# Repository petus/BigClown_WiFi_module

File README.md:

# BigClown WiFi module v1.0</br>
WiFi module for BigClown platform</br>
</br>
This WiFi module is developed for BigClown IoT platform. The WiFi module can be ESP07 or ESP12E (ESP8266 IC).</br>
</br>
How to use WiFi module for BigClown </br>
(czech language) - https://chiptron.cz/articles.php?article_id=182</br>
(english) - https://time4ee.com/articles.php?article_id=113</br>
</br>
The Wi-Fi module is supported by BigClown SDK</br>
https://github.com/bigclownlabs/bcf-sdk/blob/master/bcl/src/bc_esp8266.c</br>
Example with Wi-Fi module</br>
https://github.com/bigclownprojects/bcf-wifi-cryptoclock</br>

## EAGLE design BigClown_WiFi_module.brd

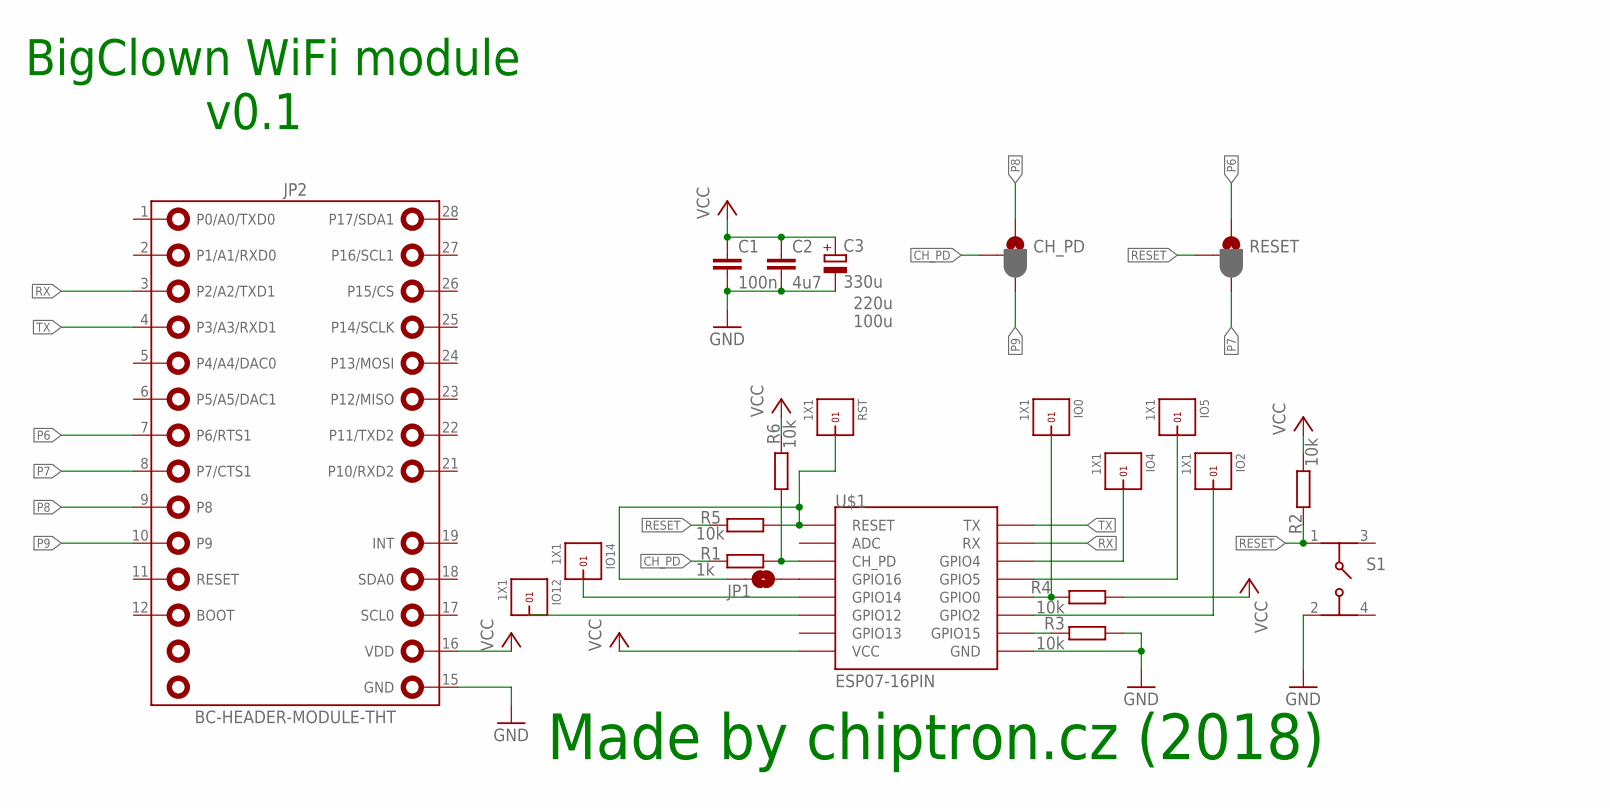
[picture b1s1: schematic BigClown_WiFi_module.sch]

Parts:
C1: 100n; C0805
C2: 4u7; C1812K
C3: 330u; D/7343-31R
CH_PD: JUMPER-SMT_3_1-NC_PASTE_SILK; SMT-JUMPER_3_1-NC_PASTE_SILK
IO0, IO2, IO4, IO5, IO12, IO14: 1X1
JP1: JUMPER-SMT_2_NO_NO-SILK; SMT-JUMPER_2_NO_NO-SILK
JP2: BC-HEADER-MODULE-THT
R1: 1k; M0805
R2, R3, R4, R5, R6: 10k; M0805
RESET: JUMPER-SMT_3_1-NC_PASTE_SILK; SMT-JUMPER_3_1-NC_PASTE_SILK
RST: 1X1
S1: 430152043826
U$1: ESP07-16PIN

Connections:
CH_PD: CH_PD.2, R1.1
GND: C1.2, C2.2, C3.-, JP2.15 (GND), R3.1, S1.2, U$1.GND
unnamed: R1.2, R6.1, U$1.CH_PD
unnamed: IO0.1, R4.2, U$1.GPIO0
unnamed: R3.2, U$1.GPIO15
unnamed: JP1.1, R5.2, RST.1, U$1.REST (RESET)
unnamed: JP1.2, U$1.GPIO16
unnamed: IO12.1, U$1.GPIO12
unnamed: IO14.1, U$1.GPIO14
unnamed: IO4.1, U$1.GPIO4
unnamed: IO5.1, U$1.GPIO5
unnamed: IO2.1, U$1.GPIO2
P6: JP2.7 (P6/RTS1), RESET.1
P7: JP2.8 (P7/CTS1), RESET.3
P8: CH_PD.1, JP2.9 (P8)
P9: CH_PD.3, JP2.10 (P9)
RESET: R2.1, R5.1, RESET.2, S1.1
RX: JP2.3 (P2/A2/TXD1), U$1.RX
TX: JP2.4 (P3/A3/RXD1), U$1.TX
VCC: C1.1, C2.1, C3.+, JP2.16 (VDD), R2.2, R4.1, R6.2, U$1.VCC

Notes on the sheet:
BigClown WiFi module
v0.1
Made by chiptron.cz (2018)
100u
220u

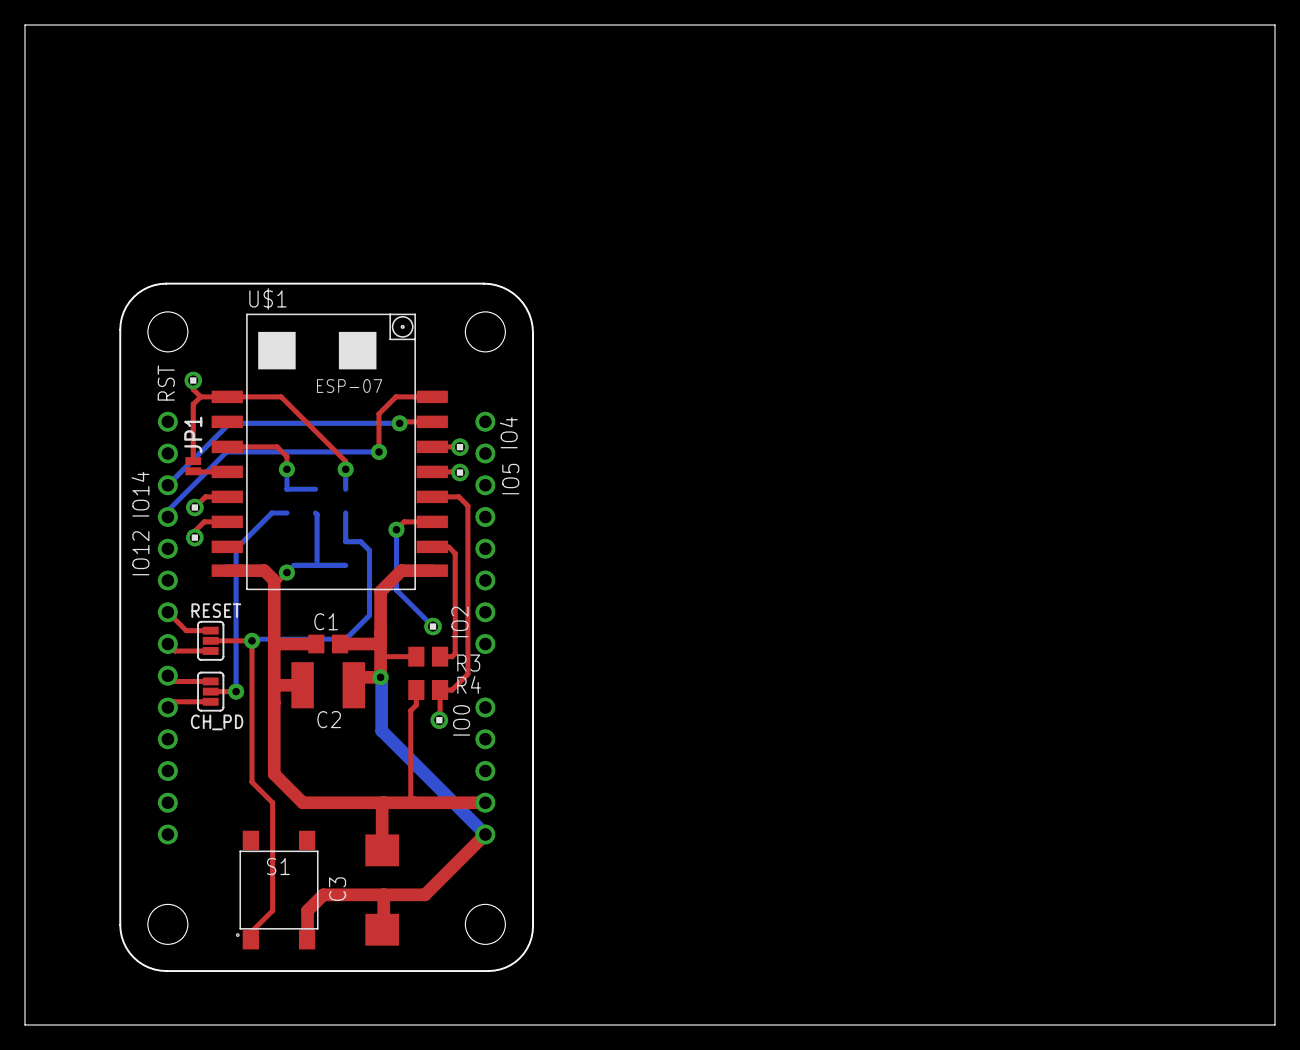
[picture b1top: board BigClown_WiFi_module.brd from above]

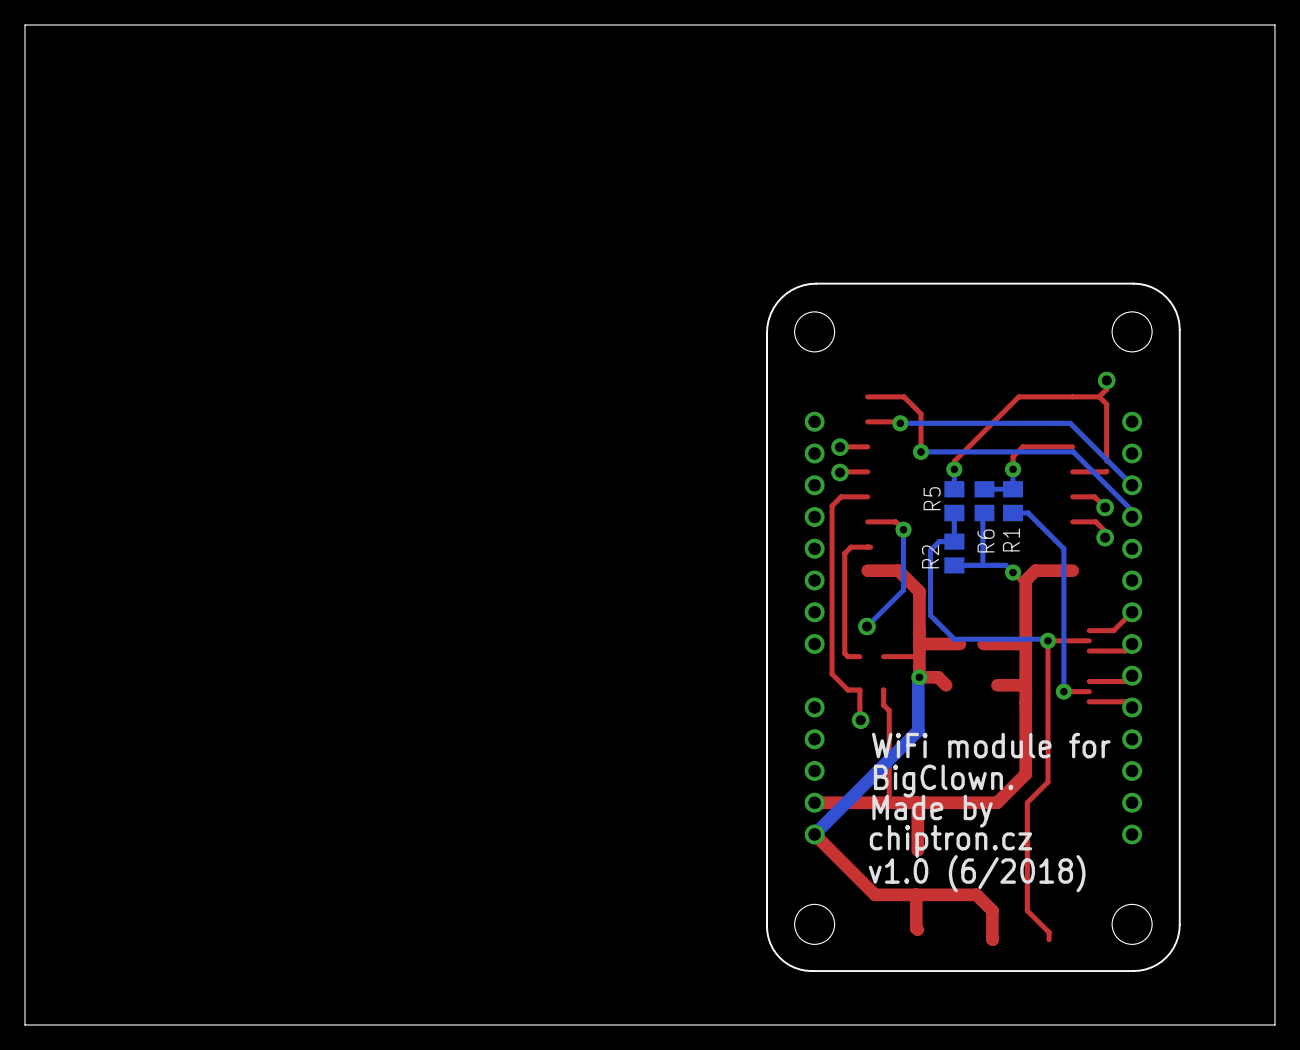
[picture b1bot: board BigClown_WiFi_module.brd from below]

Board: 2 copper layers, 99.8 x 79.8 mm, 22 parts (4 on the bottom side), 20 nets.

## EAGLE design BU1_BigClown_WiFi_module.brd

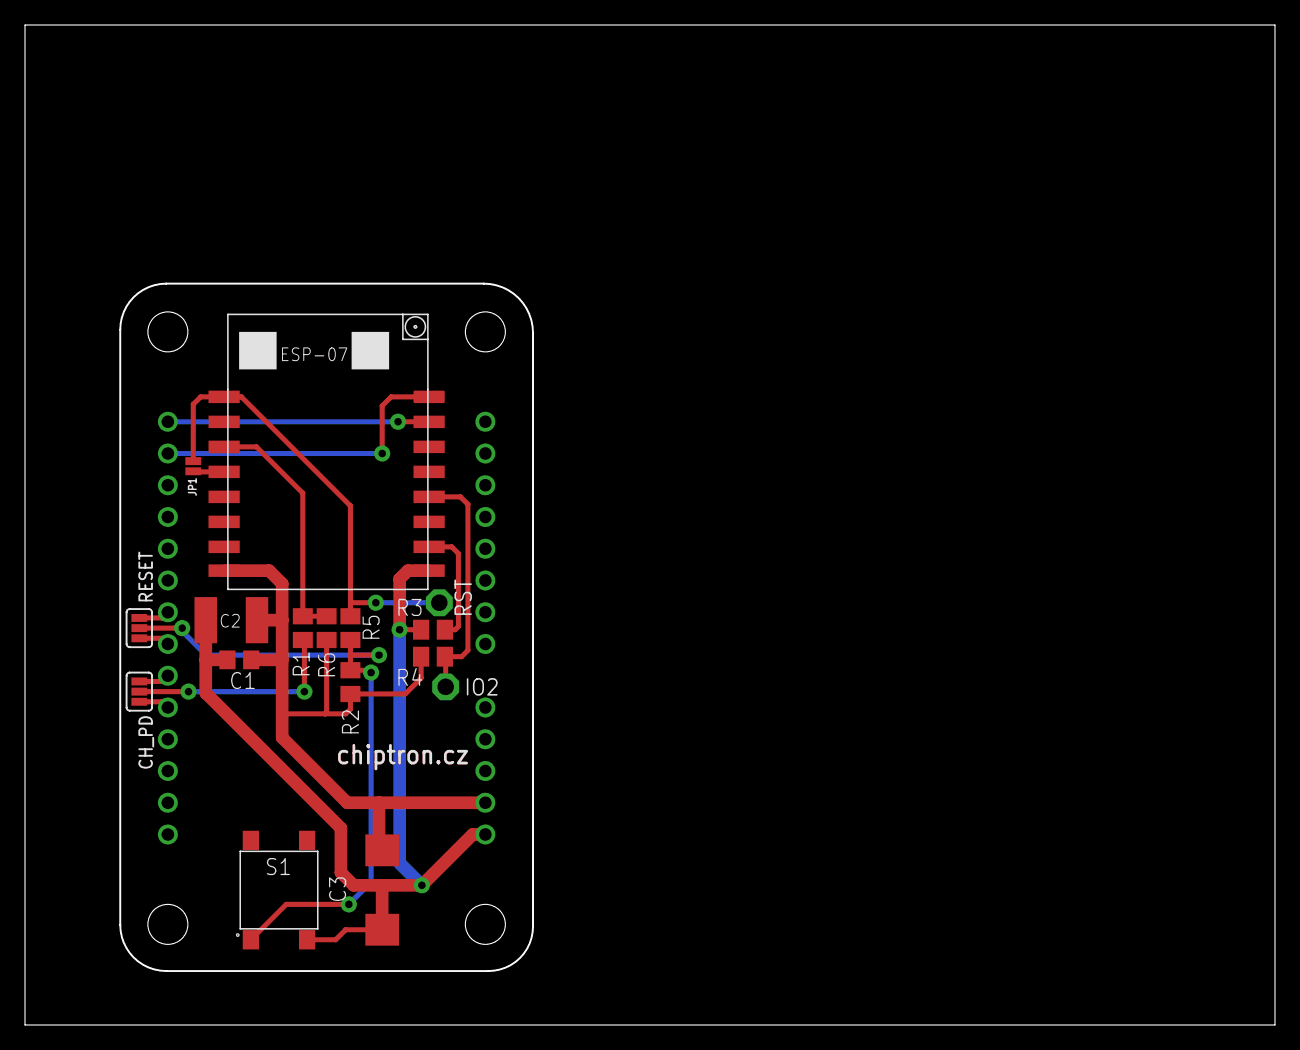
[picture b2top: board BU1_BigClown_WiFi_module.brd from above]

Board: 2 copper layers, 99.8 x 79.8 mm, 17 parts (0 on the bottom side), 15 nets.

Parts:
C1: 100n; C0805
C2: 4u7; C1812K
C3: 330u; D/7343-31R
CH_PD: JUMPER-SMT_3_1-NC_PASTE_SILK; SMT-JUMPER_3_1-NC_PASTE_SILK
IO2: PTR1PAD1-13; P1-13
JP1: JUMPER-SMT_2_NO_NO-SILK; SMT-JUMPER_2_NO_NO-SILK
JP3: BC-MODULE-CORE
R1, R2, R3, R4, R5, R6: 10k; M0805
RESET: JUMPER-SMT_3_1-NC_PASTE_SILK; SMT-JUMPER_3_1-NC_PASTE_SILK
RST: PTR1PAD1-13; P1-13
S1: 430152043826
U$1: ESP07-16PIN

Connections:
CH_PD: CH_PD.2, R1.1
GND: C1.2, C2.2, C3.-, JP3.15, R3.1, S1.2, U$1.GND
unnamed: R1.2, R6.1, U$1.CH_PD
unnamed: IO2.TP, R4.2, U$1.GPIO0
unnamed: R3.2, U$1.GPIO15
unnamed: JP1.1, R5.2, RST.TP, U$1.REST
unnamed: JP1.2, U$1.GPIO16
P6: JP3.7, RESET.1
P7: JP3.8, RESET.3
P8: CH_PD.1, JP3.9
P9: CH_PD.3, JP3.10
RESET: R2.1, R5.1, RESET.2, S1.1
RX: JP3.1, U$1.RX
TX: JP3.2, U$1.TX
VCC: C1.1, C2.1, C3.+, JP3.16, R2.2, R4.1, R6.2, U$1.VCC

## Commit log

2018-06-06 Add files via upload
    The initial commit of WiFi module for BigClown
2018-06-06 Add files via upload
    new version of design
2018-06-07 v1.0
    added pins for gpio
    added labels
2018-08-24 Add files via upload
    AT test
2018-09-29 first commit
    Temperature from TMP112 sensor is sent to tmep.eu with WiFi module

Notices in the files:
parts and their libraries:
SparkFun-Jumpers: Licensing: Creative Commons ShareAlike 4.0 International - https://creativecommons.org/licenses/by-sa/4.0
Wurth_Elektronik_Electromechanic_Switch_: Copyright: Würth Elektronik
